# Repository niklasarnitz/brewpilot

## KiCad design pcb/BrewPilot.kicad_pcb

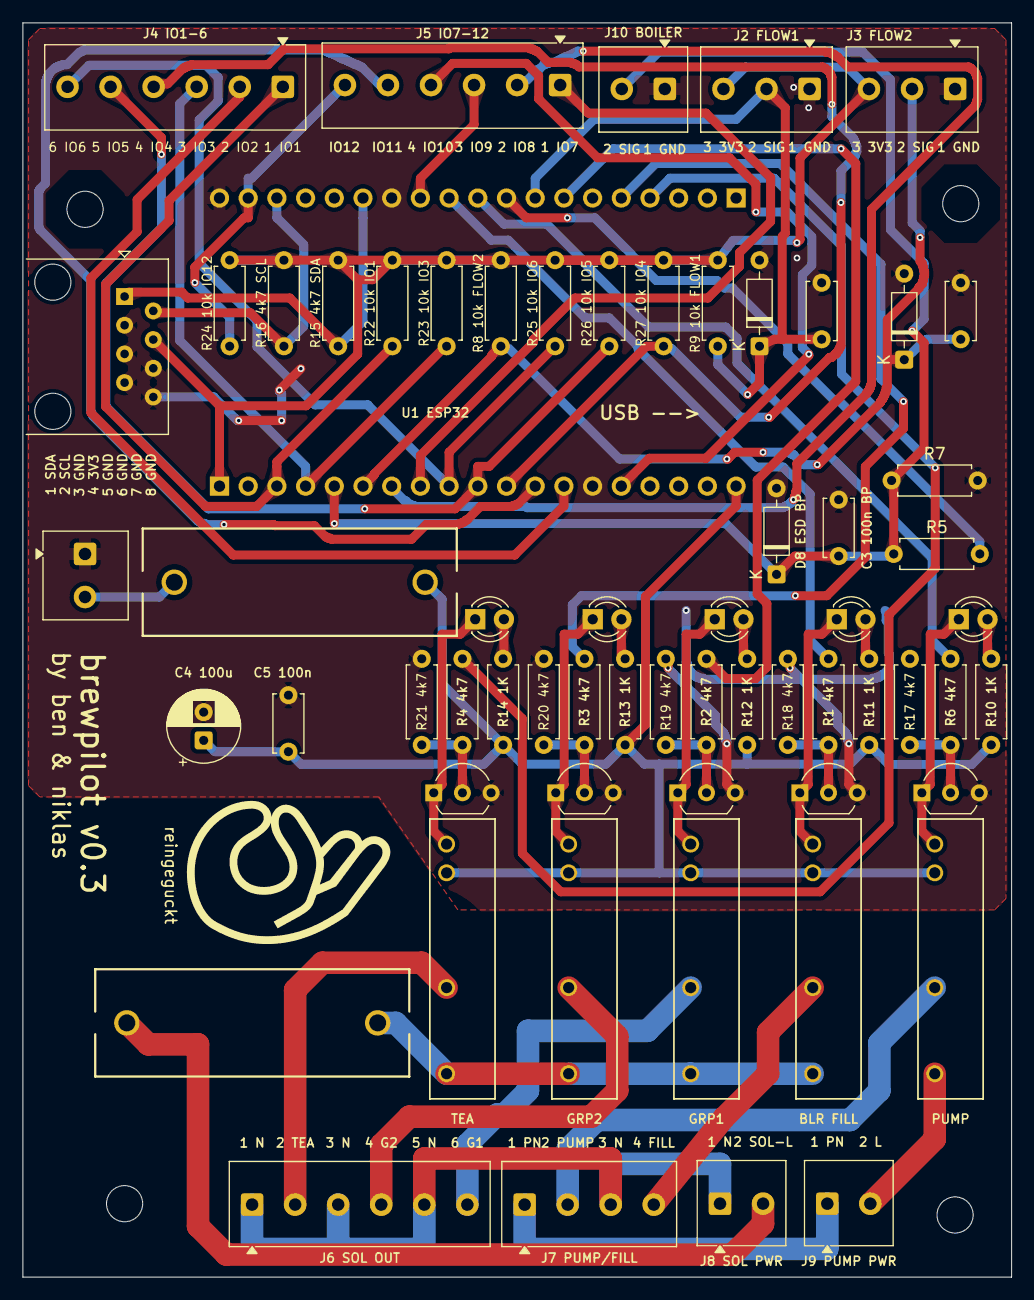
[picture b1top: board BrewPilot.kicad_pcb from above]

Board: 2 copper layers, 87.5 x 111.0 mm, 68 parts (0 on the bottom side), 52 nets.

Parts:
C1, C2: 1nF; C_Disc_D5.0mm_W2.5mm_P5.00mm
C3, C5: 100nF; C_Disc_D5.0mm_W2.5mm_P5.00mm
C4: 100uF; CP_Radial_D6.3mm_P2.50mm
D1: PUMP_ON; LED_D3.0mm
D2: BOILER_FILL_ON; LED_D3.0mm
D3: GROUP1_ON; LED_D3.0mm
D4: GROUP2_ON; LED_D3.0mm
D5: TEA_ON; LED_D3.0mm
D6, D7, D8: BZX55C5V1; D_DO-35_SOD27_P7.62mm_Horizontal
H1, H2, H3, H4: MountingHole_3.2mm_M3
J1: 5V Power; TerminalBlock_Phoenix_MKDS-1-2-3.81_1x02_P3.81mm_Horizontal
J2: Flow Meter Group One; TerminalBlock_Phoenix_MKDS-1-3-3.81_1x03_P3.81mm_Horizontal
J3: Flow Meter Group Two; TerminalBlock_Phoenix_MKDS-1-3-3.81_1x03_P3.81mm_Horizontal
J4: FlexGPIO_1; TerminalBlock_Phoenix_MKDS-1-6-3.81_1x06_P3.81mm_Horizontal
J5: FlexGPIO_2; TerminalBlock_Phoenix_MKDS-1-6-3.81_1x06_P3.81mm_Horizontal
J6: RelayOut_1; TerminalBlock_Phoenix_MKDS-1-6-3.81_1x06_P3.81mm_Horizontal
J7: RelayOut2; TerminalBlock_Phoenix_MKDS-1-4-3.81_1x04_P3.81mm_Horizontal
J8: Solenoid Power; TerminalBlock_Phoenix_MKDS-1-2-3.81_1x02_P3.81mm_Horizontal
J9: Pump Power; TerminalBlock_Phoenix_MKDS-1-2-3.81_1x02_P3.81mm_Horizontal
J10: Boiler Probe; TerminalBlock_Phoenix_MKDS-1-2-3.81_1x02_P3.81mm_Horizontal
J11: SOL_L_FUSE; BLX-A_5x20mm
J12: 5V_FUSE_5x20mm; BLX-A_5x20mm
J13: I2C Port; RJ45_Amphenol_54602-x08_BoardEdge
K1, K2, K3, K4, K5: G3MB-202P DC5; G3MB-202P DC5_OMR
Q1, Q2, Q3, Q4, Q5: BC547; TO-92_Inline_Wide
R1, R2, R3, R4, R6, R15, R16, R17, R18, R19, R20, R21: 4.7k; R_Axial_DIN0207_L6.3mm_D2.5mm_P7.62mm_Horizontal
R5, R7, R8, R9, R22, R23, R24, R25, R26, R27: 10k; R_Axial_DIN0207_L6.3mm_D2.5mm_P7.62mm_Horizontal
R10, R11, R12, R13, R14: 1k; R_Axial_DIN0207_L6.3mm_D2.5mm_P7.62mm_Horizontal
U1: esp32; esp32_38pin

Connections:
5V_RAW: J1.2, J12.1
+3.3V: J2.3, J3.3, J13.4, R8.2, R9.2, R15.1, R16.1, R22.1, R23.1, R24.1, R25.1, R26.1, R27.1, U1.1 (3.3V)
+5V: C4.1, C5.1, J12.2, K1.3, K2.3, K3.3, K4.3, K5.3, R10.1, R11.1, R12.1, R13.1, R14.1, U1.19 (5V)
AC_PUMP_NEUTRAL: J7.1, J9.1
AC_PUMP_PHASE: J9.2, K1.1
AC_PUMP_POWER_OUT: J7.2, K1.2
AC_SOLENOID_BOILER_FILL: J7.4, K2.2
AC_SOLENOID_GROUP_ONE: J6.6, K3.2
AC_SOLENOID_GROUP_TWO: J6.4, K4.2
AC_SOLENOID_NEUTRAL: J6.1, J6.3, J6.5, J7.3, J8.1
AC_SOLENOID_PHASE: J11.2, K2.1, K3.1, K4.1, K5.1
AC_SOLENOID_TEA: J6.2, K5.2
CONTROL_RELAY_BOILER_FILL: R1.2, U1.30 (GPIO18)
CONTROL_RELAY_GROUP_ONE: R2.1, U1.26 (GPIO4)
CONTROL_RELAY_GROUP_TWO: R3.2, U1.24 (GPIO2)
CONTROL_RELAY_PUMP: R6.2, U1.29 (GPIO5)
CONTROL_RELAY_TEA: R4.2, U1.23 (GPIO15)
FLEXIBLE_IO_01: J4.1, R22.2, U1.3 (GPI36)
FLEXIBLE_IO_02: J4.2, U1.13 (GPIO12)
FLEXIBLE_IO_03: J4.3, R23.2, U1.4 (GPI39)
FLEXIBLE_IO_04: J4.4, R27.2, U1.11 (GPIO27)
FLEXIBLE_IO_05: J4.5, R26.2, U1.10 (GPIO26)
FLEXIBLE_IO_06: J4.6, R25.2, U1.9 (GPIO25)
FLEXIBLE_IO_07: J5.1, U1.8 (GPIO33)
FLEXIBLE_IO_08: J5.2, U1.7 (GPIO32)
FLEXIBLE_IO_09: J5.3, U1.31 (GPIO19)
FLEXIBLE_IO_10: J5.4, U1.15 (GPIO13)
FLEXIBLE_IO_11: J5.5, U1.12 (GPIO14)
FLEXIBLE_IO_12: J5.6, R24.2, U1.37 (GPIO23)
GND: C1.2, C2.2, C3.2, C4.2, C5.2, D6.2, D7.2, D8.2, J1.1, J2.1, J3.1, J10.1, J13.3, J13.5, J13.6, J13.7, J13.8, Q1.3 (E), Q2.3 (E), Q3.3 (E), Q4.3 (E), Q5.3 (E), R7.2, R17.2, R18.2, R19.2, R20.2, R21.2, U1.14 (GND), U1.32 (GND), U1.38 (GND)
I2C_SCL: J13.2, R16.2, U1.36 (GPIO22)
I2C_SDA: J13.1, R15.2, U1.33 (GPIO21)
IN_BOILER_PROBE: C3.1, D8.1, J10.2, R5.1, R7.1, U1.5 (GPI34)
IN_FLOWMETER_GROUP_ONE: C1.1, D6.1, J2.2, R9.1, U1.27 (GPIO16)
IN_FLOWMETER_GROUP_TWO: C2.1, D7.1, J3.2, R8.1, U1.6 (GPI35)
LED_BOILER_FILL_A: D2.2, R11.2
LED_GROUP1_A: D3.2, R12.2
LED_GROUP2_A: D4.2, R13.2
LED_PUMP_A: D1.2, R10.2
LED_TEA_A: D5.2, R14.2
unnamed: Q1.2 (B), R6.1, R17.1
unnamed: Q2.2 (B), R1.1, R18.1
unnamed: Q3.2 (B), R2.2, R19.1
unnamed: Q4.2 (B), R3.1, R20.1
unnamed: Q5.2 (B), R4.1, R21.1
OUT_BOILER_PROBE_VOLTAGE: R5.2, U1.28 (GPIO17)
SOL_L: J8.2, J11.1
SSR_BOILER_FILL_SINK: D2.1, K2.4, Q2.1 (C)
SSR_GROUP1_SINK: D3.1, K3.4, Q3.1 (C)
SSR_GROUP2_SINK: D4.1, K4.4, Q4.1 (C)
SSR_PUMP_SINK: D1.1, K1.4, Q1.1 (C)
SSR_TEA_SINK: D5.1, K5.4, Q5.1 (C)

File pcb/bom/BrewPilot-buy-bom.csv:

"Item","Order Qty","References / Location","Value / Rating","Description","Manufacturer","Manufacturer Part Number","Status / Note"
"1","1","PCB1","BrewPilot","Bare printed circuit board","Custom","BrewPilot.kicad_pcb","Specify stack-up, finish, copper weight, and fabrication quantity."
"2","2","C1, C2","1 nF, 50 V, C0G, ±5%","Radial dipped ceramic capacitor, 5.00 mm pitch","TDK","FG28C0G1H102JNT06","Ready to order."
"3","2","C3, C5","100 nF, 50 V, X7R, ±10%","Radial dipped ceramic capacitor, 5.00 mm pitch","TDK","FG28X7R1H104KNT06","Ready to order."
"4","1","C4","100 µF, 16 V, ±20%, 105 °C","Radial aluminum electrolytic capacitor, 6.3 mm diameter","Panasonic Industry","EEU-FR1C101B","Ready to order."
"5","5","D1, D2, D3, D4, D5","Green, 3 mm","Diffused through-hole indicator LED","Kingbright","L-934GD","Green is proposed; the schematic does not define color."
"6","3","D6, D7, D8","5.1 V, 500 mW","Axial Zener clamp diode, DO-35","Vishay","BZX55C5V1-TR","Ready to order; pragmatic THT input clamp."
"11","1","J11","5 × 20 mm, 250 VAC","Covered PCB fuse holder","BLX-A (verify supplier)","BLX-A","Check supplier dimensions and mains safety rating before ordering."
"12","1","J12","5 × 20 mm","Covered PCB fuse holder","BLX-A (verify supplier)","BLX-A","Check supplier dimensions before ordering."
"13","1","J13","8P8C, right angle","Unshielded through-hole modular jack","Amphenol Communications Solutions","54602-908LF","Ready to order."
"15","5","Q1, Q2, Q3, Q4, Q5","BC547B","NPN transistor, TO-92, C-B-E pin order","onsemi","BC547BTA","Ready to order."
"16","7","R1, R2, R3, R4, R6, R15, R16","4.7 kΩ, ±5%, 0.25 W","Axial carbon-film resistor","Yageo","CFR-25JB-52-4K7","Ready to order."
"17","2","R5, R7","10 kΩ, ±1%, 0.4 W","Miniature axial metal-film resistor","Vishay Beyschlag","MBA02040C1002FC100","Form leads to 7.62 mm pitch and mount horizontally; verify lead reach."
"18","2","R8, R9","10 kΩ, ±5%, 0.25 W","Axial carbon-film resistor","Yageo","CFR-25JB-52-10K","Ready to order."
"19","5","R10, R11, R12, R13, R14","1 kΩ, ±5%, 0.25 W","Axial carbon-film resistor","Yageo","CFR-25JB-52-1K","Ready to order."
"22","1","Installed in J11","TBD, 5 × 20 mm, 250 VAC minimum","Solenoid mains fuse element","TBD","TBD","Blocked until load/inrush and wire-gauge review defines current and time characteristic."
"23","1","Installed in J12","TBD, 5 × 20 mm","5 V input fuse element","TBD","TBD","Blocked until maximum supply current and wire-gauge review defines current and time characteristic."

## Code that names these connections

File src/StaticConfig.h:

//
// Created by Niklas Arnitz on 11.11.24.
//

#ifndef BREWPILOT_CONFIG_H
#define BREWPILOT_CONFIG_H

#define DEBUG true

// Pins
// Outputs
#define RELAY_PUMP 5
#define RELAY_GROUP_ONE 4
#define RELAY_GROUP_TWO 2
#define RELAY_BOILER_FILL 18
#define RELAY_TEA 15

// Inputs
// Keyboard Matrix
#define FLEXIBLE_IO_1 36
#define FLEXIBLE_IO_2 12
#define FLEXIBLE_IO_3 39
#define FLEXIBLE_IO_4 27
#define FLEXIBLE_IO_5 26
#define FLEXIBLE_IO_6 25
#define FLEXIBLE_IO_7 33
#define FLEXIBLE_IO_8 32
#define FLEXIBLE_IO_9 19
#define FLEXIBLE_IO_10 13
#define FLEXIBLE_IO_11 14
#define FLEXIBLE_IO_12 23

// Boiler Probe
#define BOILER_PROBE_PIN 34
#define OUT_BOILER_VOLTAGE 17

// Flow Meters
#define GROUP_ONE_FLOW_METER_PIN 16
#define GROUP_TWO_FLOW_METER_PIN 35

// Boiler Stuff
#define BOILER_FILL_LEVEL 1000 // Value for the LaCimbali M29 Select DT2 / R

#endif // BREWPILOT_CONFIG_H

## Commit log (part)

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2024-10-31 added gitignore
2024-11-08 implemented initial beginnings of logic
2024-11-08 moved one small thing around
2024-11-10 Moved state to a global state object
2024-11-11 big refactoring in preparation for multi threading
2024-11-17 minor changes
2025-03-16 added button code
2025-03-17 some more updates
2025-03-17 added docs for electronics (relays, solenoids)
2025-03-19 more small updates
2025-03-19 cleanup
2025-03-19 corrected some pins
2025-03-20 stash
2025-04-03 the machine works :party:
2025-04-05 this stuffs now works
2025-04-05 volumetrics wokrs
2025-04-08 added prototype mounting plate code
2025-04-16 addressed issues raised in review
2025-04-16 replaced enums with enum class
2025-04-16 some more fixes
2025-04-23 added the fallback to stop extracting tea water
2025-04-23 resolved one more todo
2025-04-23 some more sonarqube fixes
2025-04-28 added some documentation
2025-04-28 added initial pwa and ble functionality
2025-11-10 feature: auto backflush
2025-11-11 chore: added machine specific settings for easier creation of new machine profiles
2025-11-11 fixed some small issues
2025-11-11 fixed
2025-11-11 another one
2025-11-25 moved m29 code to another piece of code
2025-12-19 updated the code to support the rancilio s27
2025-12-19 added the first draft of the pcb
2025-12-19 fixed two small things
2025-12-19 Initial plan
2025-12-27 simplified boiler state handler
2025-12-28 skip processing when read is only prepared
2025-12-29 skip processing when read is only prepared (#15)
2025-12-29 more consistent logging
2025-12-29 more consistent logging (#16)
2026-01-04 auto backfush works
    it starts as soon as both buttons are pressed and it ends after last extraction instead of awaiting another pause
2026-01-04 feat: add BLE interface for machine control and settings
    - Add NimBLE-Arduino library dependency for BLE communication
    - Create BLEService class to manage BLE characteristics and advertising
    - Broadcasts machine state (boiler, group heads, tea water, programming mode)
    - Allows remote reading and writing of backflush cycle times
    - Uses GATT characteristics for state notifications
    - Create BLECoreManager to run BLE operations on ESP32 core 1
2026-01-04 docs: add comprehensive BLE enhancement analysis and roadmap
    - BLE_Enhancement_Analysis.md: detailed breakdown of 25+ features that could be exposed via BLE
    - Current implementation vs proposed additions
    - Real-time monitoring capabilities (flow meters, boiler state)
    - Settings management (volumetrics, auto-backflush, backflush timing)
    - Remote control features (programming mode, relay states)
    - Diagnostic and telemetry options
2026-01-04 docs: add BLE component interaction and architecture details
    - Detailed component overview and dependencies
    - Characteristic ownership and update patterns
    - File dependency chart
    - Real-time data update frequencies and strategy
    - Thread safety analysis (no mutex needed for current design)
    - Performance impact analysis (memory, CPU, bandwidth)
2026-01-04 docs: add executive summary of BLE feature analysis
    - Overview of 26 potential BLE features across 4 priority levels
    - Summary statistics: 3 done, 7 high-priority, 8 medium, 11 low
    - Detailed breakdown of each priority tier with implementation time
    - Data organization strategy for preference keys
    - Architecture considerations (thread safety, memory, performance)
    - Mobile app use cases for each implementation phase
2026-01-04 docs: add BLE documentation index and navigation guide
    - Quick start guide for decision makers, developers, and app developers
    - Complete feature inventory organized by priority (26 features total)
    - 4-phase implementation roadmap with time estimates
    - Top recommendations based on available time
    - Architecture overview and key files reference
    - Mobile app integration examples (current and future)
2026-01-06 review comments: can cancel auto flushing
    cancel auto flushing with continuous button, don't enable auto flushing when in programming mode, ignore pulses in auto flushing mode, reset pulse counter and target when auto flushing
2026-01-11 updated many things
2026-01-11 fixed duplicated code
2026-01-11 added minimal handler for a scale
2026-01-11 add AcaiaArduinoBLE dependency
2026-01-11 added memory management and moved ble to the main task
2026-01-11 refactored StateActor
2026-01-11 refactored Relay
2026-01-11 refactored Solenoid
2026-01-11 refactored LaCimbaliM29ButtonMatrixHandler
2026-01-11 refactored RancilioS27ButtonMatrixHandler
2026-01-11 refactored ButtonHandler
2026-01-11 refactored ButtonMatrixHandler
2026-01-13 refactored GroupHeadButtonHandler
2026-01-13 refactored InputHandler
2026-01-13 refactored MachineButtonMatrixHandler
2026-01-13 refactored GroupHeadHandler
2026-01-13 refactored BoilerStateHandler
2026-01-13 refactored PreferenceHelper
2026-01-13 refactored VolumetricsHelper
2026-01-13 refactored noop
2026-01-13 refactored BLEService
2026-01-13 refactored BLECoreManager
2026-01-13 fix: add missing include and inline getMachineConfig
2026-01-13 fix getMachineConfig compiler error
2026-01-15 fixed many ble bugs
2026-01-15 updated bleservice
2026-01-15 more ble fixes
2026-01-15 fixed issues raised by sonarqube
2026-01-15 fixed more issues raised by sonarqube
2026-01-15 replaced #define with constexpr
2026-01-15 fixed other sonarqube problem
2026-01-15 fixed another sonarqube problem
2026-01-15 fixed many sonarqube problems
2026-01-15 more fixes
2026-01-15 fixed build issues
2026-01-15 more sonarqube fixes
2026-01-15 fixed many stuff
2026-01-15 fixed communication stuff and backflushing
2026-01-15 fixed sonarqube issue
2026-01-15 fixed some stuff after merge
2026-01-28 fixed shit
2026-01-28 added more stuff
2026-02-24 some more pcb additions
2026-05-20 implemented more fixes and initial clean routing pass of the pcb
2026-06-03 pcb updates
